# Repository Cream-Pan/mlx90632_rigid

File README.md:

<div id="top"></div>

# MLX90632_rigid

MLX90632を用いた非接触温度計測用リジッド基板である．
耳装着型デバイスへの組み込みを想定し，鼓膜近傍温度および周辺温度の取得を目的として設計した．

## 使用技術一覧

## 目次

1. [概要](#概要)
2. [基板仕様](#基板仕様)
3. [回路構成](#回路構成)
4. [ディレクトリ構成](#ディレクトリ構成)
5. [Git管理方針](#git管理方針)
6. [製造データ](#製造データ)
7. [設計上の注意](#設計上の注意)

## 概要

本リポジトリは，MLX90632を搭載したリジッド基板のKiCadプロジェクトを管理するためのものである．
MLX90632は，小型の非接触赤外線温度センサであり，センサ内部のEEPROMに保存された校正定数と測定データを用いて，外部マイコン側で対象物温度およびセンサ温度を算出する．

本基板では，耳装着型デバイスへの組み込みを想定し，MLX90632を小型リジッド基板上に実装する．

<p align="right">(<a href="#top">トップへ</a>)</p>

---

## 基板仕様

| 項目        | 内容                     |
| --------- | ---------------------- |
| 基板名       | MLX90632_rigid         |
| センサ       | MLX90632               |
| 通信方式      | I2C                    |
| 標準I2Cアドレス | 0x3A                   |
| 電源電圧      | 3.3 V                  |
| 視野角       | 50°                    |
| 用途        | 非接触温度計測，鼓膜近傍温度推定，熱環境評価 |
| 設計ツール     | KiCad                  |

<p align="right">(<a href="#top">トップへ</a>)</p>

---

## 回路構成

本基板は，MLX90632と外部マイコンをI2Cで接続する構成である．

```text
MCU
├── SDA
└── SCL

MLX90632
├── Thermopile
├── Ambient Temperature Sensor
├── ADC
├── RAM
└── EEPROM
```

MLX90632では，センサ内部のRAMに保存された測定データとEEPROM内の校正定数を用いて，外部マイコン側で温度を計算する．

<p align="right">(<a href="#top">トップへ</a>)</p>

---

## ディレクトリ構成

```text
.
├── .git/
├── .gitignore
├── .history/                         # VSCode等の履歴フォルダ，Git管理対象外
├── jlcpcb/                           # JLCPCB発注用データ
├── MLX90632_rigid-backups/           # KiCadバックアップ，Git管理対象外
├── fp-info-cache                     # KiCadキャッシュ，Git管理対象外
├── MLX90632_rigid.kicad_pcb          # PCBレイアウト
├── MLX90632_rigid.kicad_prl          # KiCadローカル設定，Git管理対象外
├── MLX90632_rigid.kicad_pro          # KiCadプロジェクト
└── MLX90632_rigid.kicad_sch          # 回路図
```

基本的に，Gitで管理する主要ファイルは以下である．

```text
MLX90632_rigid.kicad_pro
MLX90632_rigid.kicad_sch
MLX90632_rigid.kicad_pcb
.gitignore
README.md
```

<p align="right">(<a href="#top">トップへ</a>)</p>

---

## Git管理方針

本リポジトリでは，KiCadプロジェクト本体をGitで管理し，自動生成ファイルや個人環境依存ファイルは管理対象外とする．

主に以下をGit管理対象外とする．

```text
*.kicad_prl
fp-info-cache
*-backups/
*_backups/
*.bak
*-bak
_autosave-*
*.lck
.history/
```

また，製造出力ファイルも基本的には自動生成物として扱う．

```text
*.gbr
*.drl
*.pos
*.rpt
*.zip
```

本プロジェクトでは，自作シンボルおよび自作フットプリントを `kicad_my_library` リポジトリで管理している．  
KiCadで本プロジェクトを開く前に，`kicad_my_library` をcloneし，KiCadのライブラリ設定に登録する必要がある．

```powershell
git clone https://github.com/Cream-Pan/kicad_my_library.git
```

登録するライブラリは以下である．

```text
Footprint Library:
kicad_my_library/footprints/MyLibrary.pretty

Symbol Library:
kicad_my_library/symbols/MyLibrary.kicad_sym
```

KiCad上でのライブラリNicknameは以下に統一する．
```text
MyLibrary
```

Nicknameを変更すると，MyLibrary:C0603 のような既存の参照が壊れる可能性がある．

発注時点の製造データを残す場合は，必要に応じてGitHub Releasesや別フォルダで管理する．

<p align="right">(<a href="#top">トップへ</a>)</p>

---

## 製造データ

`jlcpcb` フォルダには，JLCPCBでの基板製造および部品実装を想定したデータを配置する．

主な出力対象は以下である．

* Gerber
* Drill
* BOM
* CPL

現状の `.gitignore` では，`.gbr`，`.drl`，`.zip` などの製造出力はGit管理対象外としている．
そのため，発注データをGitHub上に残したい場合は，`.gitignore` の例外設定またはGitHub Releasesでの管理を検討する．

<p align="right">(<a href="#top">トップへ</a>)</p>

---

## 設計上の注意

### 1．視野角

MLX90632は50°のFOVを持つため，筐体やカバーがセンサの視野を遮らないようにする．
特に耳装着型デバイスに組み込む場合は，センサ前面に樹脂や筐体内壁が入り込まないように設計する．

### 2．熱設計

MLX90632は非接触温度センサであり，センサ周辺の熱勾配や周辺部品の発熱が測定値に影響する．
そのため，以下に注意する．

* 発熱する部品をセンサ近傍に配置しない
* センサ周辺に急激な温度勾配を作らない
* センサ前面に汚れや遮蔽物を置かない
* 必要に応じて熱源からの距離や基板スリットを検討する

### 3．デカップリング

MLX90632の近傍にデカップリングコンデンサを配置する．
特に電源ノイズは赤外線温度計測の安定性に影響するため，VDDおよびGNDへの配線を短くする．

### 4．I2C通信

MLX90632はI2Cで通信する．
SDAおよびSCLの配線長，プルアップ抵抗，バス容量に注意する．
複数センサを同一バス上で扱う場合は，I2Cアドレスの設定にも注意する．

<p align="right">(<a href="#top">トップへ</a>)</p>

---

開発者情報
Name: Takato Ishii

Portfolio: https://takato-ishii.vercel.app/

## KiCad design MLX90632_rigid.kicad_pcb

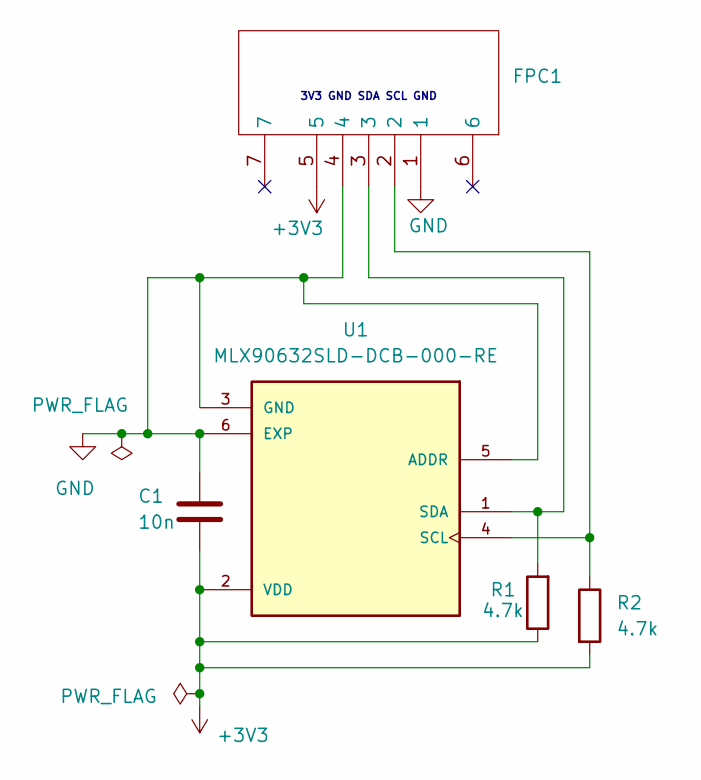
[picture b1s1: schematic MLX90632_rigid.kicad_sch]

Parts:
C1: 10n; C_0603_1608Metric
FPC1: FPC-SMD_AFC07-S05FCC-00; Manufacturer Part AFC07-S05FCC-00; LCSC Part Name 间距:0.5mm P数:5P 抽屉式 下接
R1, R2: 4.7k; R_0402_1005Metric
U1: MLX90632SLD-DCB-000-RE; MLX90632; PARTREV 12

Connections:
+3V3: C1.2, FPC1.5, R1.1, R2.2, U1.2 (VDD)
GND: C1.1, FPC1.1, FPC1.4, U1.3 (GND), U1.5 (ADDR), U1.6 (EXP)
unnamed: FPC1.2, R2.1, U1.4 (SCL)
unnamed: FPC1.3, R1.2, U1.1 (SDA)

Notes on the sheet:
3V3 GND SDA SCL GND

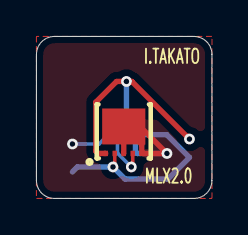
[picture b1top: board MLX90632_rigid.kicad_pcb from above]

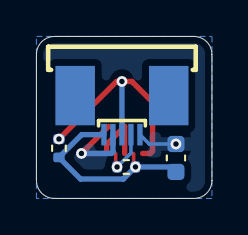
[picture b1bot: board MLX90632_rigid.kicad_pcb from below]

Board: 2 copper layers, 9.8 x 9.0 mm, 5 parts (4 on the bottom side), 4 nets.

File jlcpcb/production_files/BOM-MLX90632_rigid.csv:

Comment,Designator,Footprint,LCSC,Quantity
10n,C1,C_0603_1608Metric,C77063,1
4.7k,"R1,R2",R_0402_1005Metric,C281778,2
MLX90632SLD-DCB-000-RE,U1,MLX90632,C7541116,1
~,FPC1,FPC-SMD_AFC07-S05FCC-00,C262199,1

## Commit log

2026-06-01 Initial KiCad project
2026-06-01 Add README
2026-06-04 Update for Order
